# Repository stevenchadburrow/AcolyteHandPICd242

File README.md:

# AcolyteHandPICd242

This is the Acolyte Hand PIC'd 242, containing two PIC24 microcontrollers:  
The PIC24EP512GP202 and the PIC24FJ128GB202.  
The 'EP does all of the graphics, sound, and button inputs.  
The 'FJ is exclusively designed to be used as a USB host for HID and MSD.

The board is an all through-hole design for easy soldering.

Much of the code will be reused from the Acolyte Hand PIC'd 24 project.

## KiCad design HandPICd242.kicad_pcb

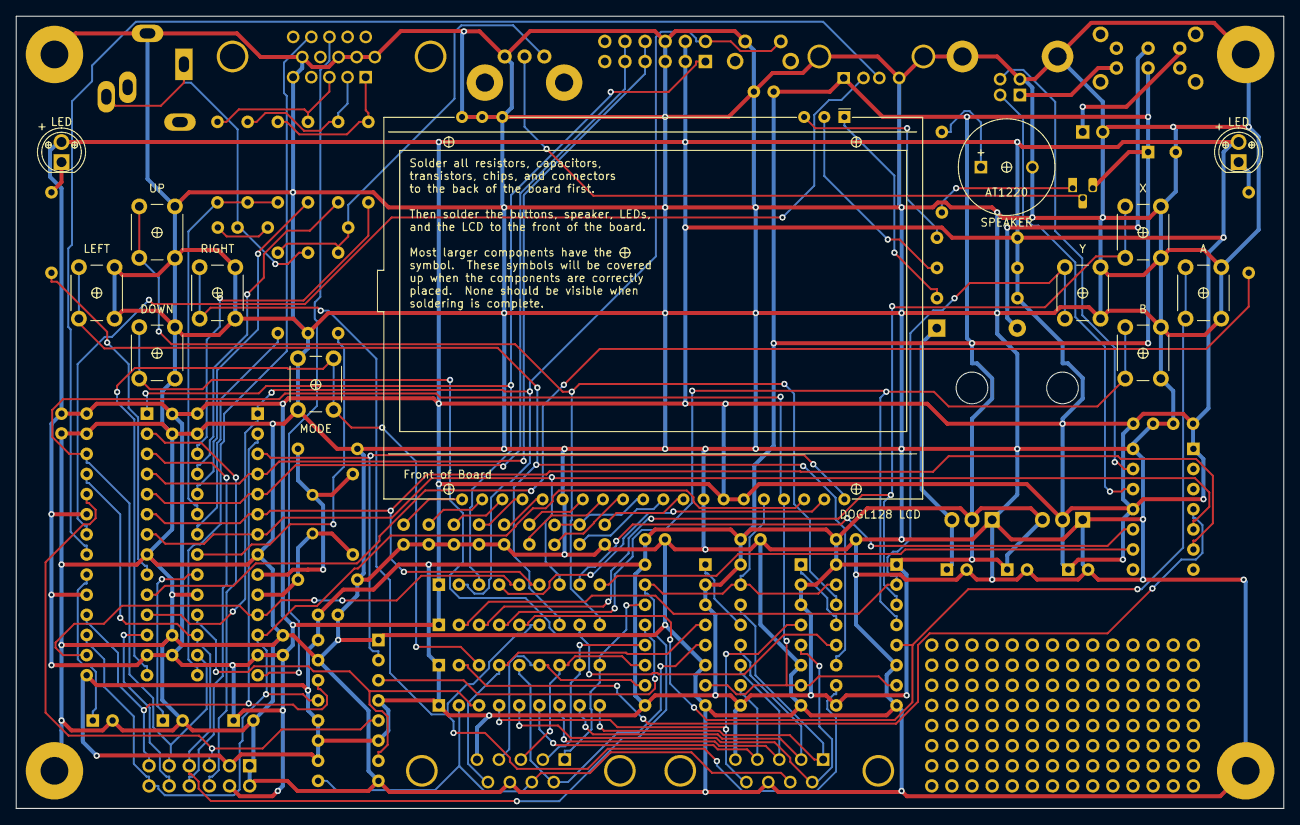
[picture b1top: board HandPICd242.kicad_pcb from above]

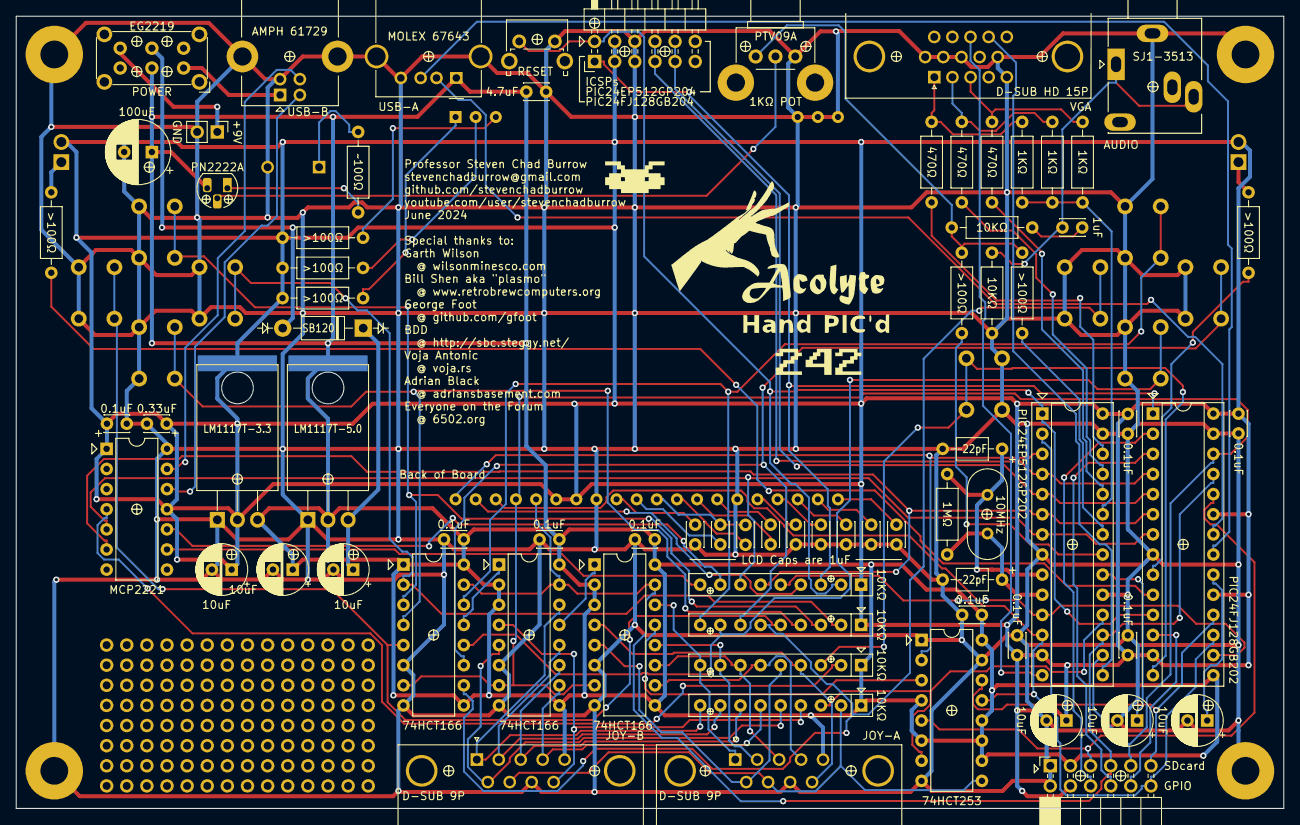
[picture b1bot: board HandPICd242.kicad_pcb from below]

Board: 2 copper layers, 160.0 x 100.0 mm, 101 parts (84 on the bottom side), 96 nets.

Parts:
C1, C2, C3, C6, C10, C13, C14, C16, C17, C18, C21, C22, C23, C24, C25, C26, C27, C28, C29, C30, C31: C_Small; C_Disc_D3.0mm_W2.0mm_P2.50mm
C4, C7, C8, C9, C12, C15: C_Polarized_Small_US; CP_Radial_D6.3mm_P2.50mm
C5: C_Polarized_US; CP_Radial_D8.0mm_P3.50mm
C19, C20: C; C_Axial_L3.8mm_D2.6mm_P7.50mm_Horizontal
D1, D2: LED; CustomLED
D3: D; D_DO-41_SOD81_P10.16mm_Horizontal
G101: LOGO; AcolyteTitle
G102: LOGO; HandPickedTitle
G103: LOGO; Mystery
G105: LOGO; ModelNum
G106: LOGO; HandPinching
J1: USB_B; USB_B_Lumberg_2411_02_Horizontal
J3: USB_A; USB_A_Molex_67643_Horizontal
J4, J19: DE9_Plug; DSUB-9_Male_Horizontal_P2.77x2.84mm_EdgePinOffset7.70mm_Hou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
J5: AudioJack3; BIGJack_3.5mm_Ledino_KB3SPRS_Horizontal
J6: DE15_Receptacle_HighDensity; DSUB-15-HD_Female_Horizontal_P2.29x2.54mm_VGA
J7: Conn_02x06_Odd_Even; PinSocket_2x06_P2.54mm_Horizontal
J9, J11, J12, J13: Conn_02x14_Odd_Even; BLANK-PinHeader_2x14_P2.54mm_Vertical
J14: Conn_02x06_Odd_Even; PinHeader_2x06_P2.54mm_Horizontal
J21: Conn_01x02; PinHeader_1x02_P2.54mm_Vertical
LS1: Speaker; MagneticBuzzer_ProSignal_ABT-410-RC
Q1: PN2222A; TO-92_HandSolder
R1, R2, R3, R4, R6, R7, R8, R9, R10, R11, R12, R13, R14, R15, R16, R18, R19: R_US; R_Axial_DIN0207_L6.3mm_D2.5mm_P10.16mm_Horizontal
RN1, RN2, RN3, RN4: R_Network08_US; R_Array_SIP9
RV1: R_Potentiometer_US; Potentiometer_Bourns_PTV09A-2_Single_Horizontal
SW1: SW_Push_DPDT; SW_E-Switch_EG2219_DPDT_Angled
SW3, SW4, SW5, SW6, SW7, SW8, SW9, SW10, SW13: SW_Push; SW_PUSH_6mm_H5mm
SW11: SW_Push; SW_Tactile_SPST_Angled_PTS645Vx83-2LFS
TP2, TP3, TP4, TP5: TestPoint; ScrewHole-4-40
U1: LM1117T-3.3; TO-220-3_Horizontal_TabDown-custom
U2: LM1117T-5.0; TO-220-3_Horizontal_TabDown-custom
U3: EA_DOGL128X-6; EA_DOGL128-6
U4: MCP2221AxSL; DIP-14_W7.62mm
U5: PIC24EP512GP202; DIP-28_W7.62mm_Socket
U6: PIC24FJ128GB202; DIP-28_W7.62mm_Socket
U7, U8, U9: 74HCT166; DIP-16_W7.62mm
U10: 74HCT253; DIP-16_W7.62mm
Y1: Crystal; Crystal_HC49-4H_Vertical

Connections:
+3V3: C1.1, C2.2, C3.2, C8.1, C12.1, C13.2, C14.2, C18.2, D1.2 (A), D2.2 (A), J7.4, J14.3, J14.4, R6.1, R18.1, R19.1, RN2.1 (common), RN4.1 (common), U1.2 (VO), U3.34 (VDD2), U3.35 (VDD), U4.1 (VDD), U4.11 (VUSB), U5.13 (VDD), U5.28 (AVDD), U6.13 (VDD), U6.19 (VBAT), U6.23 (Vusb3V3), U6.28 (VDD)
+5V: C5.1, C6.2, C15.1, C16.1, C17.1, C30.1, C31.1, J3.1 (VBUS), J4.5, J7.3, J19.5, Q1.3 (C), RN1.1 (common), RN3.1 (common), SW1.2 (B), U1.3 (VI), U2.2 (VO), U6.15 (RB6/RP6/Vbus*), U7.2 (A), U7.3 (B), U7.9 (Clr), U7.16 (VCC), U8.1 (Ds), U8.9 (Clr), U8.16 (VCC), U9.2 (A), U9.3 (B), U9.9 (Clr), U9.16 (VCC), U10.4 (I2a), U10.6 (I0a), U10.10 (I0b), U10.11 (I1b), U10.12 (I2b), U10.16 (VCC)
+9V: J21.1, SW1.6 (C)
AUDIO-COMBINED: R8.2, R9.1, R10.1, RV1.3
AUDIO-NEG: C10.2, R8.1
AUDIO-OUT: C10.1, J5.R, J5.T, R7.2
AUDIO-SOURCE-A: R10.2, U5.22 (RB11/RP43*+)
AUDIO-SOURCE-B: R9.2, U5.21 (RB10/RP42*+)
BLUE: J6.3, R13.2, R16.2
BUTTON-A: RN4.5 (R4), SW7.1, U8.5 (D)
BUTTON-B: RN4.4 (R3), SW8.1, U8.4 (C)
BUTTON-DOWN: RN4.8 (R7), SW4.1, U8.12 (G)
BUTTON-LEFT: RN4.7 (R6), SW5.1, U8.11 (F)
BUTTON-MODE: RN1.3 (R2), SW13.1, U6.14 (RB5/USBID*)
BUTTON-RIGHT: RN4.6 (R5), SW6.1, U8.10 (E)
BUTTON-UP: RN4.9 (R8), SW3.1, U8.14 (H)
BUTTON-X: RN4.3 (R2), SW9.1, U8.3 (B)
BUTTON-Y: RN4.2 (R1), SW10.1, U8.2 (A)
DS-A: U7.13 (Qh), U9.1 (Ds)
DS-B: U7.1 (Ds), U8.13 (Qh)
GND: C1.2, C2.1, C3.1, C4.2, C5.2, C6.1, C7.2, C8.2, C9.2, C12.2, C13.1, C14.1, C15.2, C16.2, C17.2, C18.1, C19.2, C20.2, C24.2, C25.2, C26.2, C27.2, C28.2, C29.2, C30.2, C31.2, J1.4 (GND), J1.5 (Shield), J3.4 (GND), J3.5 (Shield), J4.8, J5.S, J6.5, J6.6, J6.7, J6.8, J6.10, J7.1, J7.2, J14.5, J14.6, J19.8, J21.2, LS1.2, R7.1, RV1.1, SW3.2, SW4.2, SW5.2, SW6.2, SW7.2, SW8.2, SW9.2, SW10.2, SW11.2, SW13.2, TP2.1, TP3.1, TP4.1, TP5.1, U1.1 (GND), U2.1 (GND), U3.18 (C1-), U3.19 (C2-), U3.20 (C3-), U3.26 (VSS), U3.33 (VSS), U4.14 (VSS), U5.8 (VSS), U5.19 (VSS), U5.27 (AVSS), U6.8 (VSS), U6.27 (VSS), U7.6 (CE), U7.8 (GND), U8.6 (CE), U8.8 (GND), U9.6 (CE), U9.8 (GND), U10.1 (OEa), U10.8 (GND), U10.15 (OEb)
GPIO-RA0: J7.6, U6.2 (RA0/RP5/PGED3/ASDA1)
GPIO-RA1: J7.8, U6.3 (RA1/RP6/PGEC3/ASCL1)
GPIO-RA4: J7.10, U6.12 (RA4*)
GREEN: J6.2, R12.2, R15.2
H-SYNC: J6.13, U5.14 (RB5/RP37/ASDA2/PGED2*)
ICSP-CLK: J14.9, J14.10, U5.5 (RB1/RPI33/PGEC3), U6.5 (RB1/RP1/PGEC1)
ICSP-DAT: J14.7, J14.8, U5.4 (RB0/RPI32/PGED3), U6.4 (RB0/RP0/PGED1)
INTERRUPT: RN2.5 (R4), U5.11 (RB4/RP36*), U6.16 (RB7/RP7/INT0*)
JOY-BUTTON1-A: J4.6, RN1.5 (R4), U9.5 (D)
JOY-BUTTON1-B: J19.6, RN3.5 (R4), U7.5 (D)
JOY-BUTTON2-A: J4.9, RN1.4 (R3), U9.4 (C)
JOY-BUTTON2-B: J19.9, RN3.4 (R3), U7.4 (C)
JOY-DOWN-A: J4.2, RN1.8 (R7), U9.12 (G)
JOY-DOWN-B: J19.2, RN3.8 (R7), U7.12 (G)
JOY-LEFT-A: J4.3, RN1.7 (R6), U9.11 (F)
JOY-LEFT-B: J19.3, RN3.7 (R6), U7.11 (F)
JOY-RIGHT-A: J4.4, RN1.6 (R5), U9.10 (E)
JOY-RIGHT-B: J19.4, RN3.6 (R5), U7.10 (E)
JOY-SELECT: J4.7, J19.7, RN3.2 (R1), U10.9 (Zb)
JOY-UP-A: J4.1, RN1.9 (R8), U9.14 (H)
JOY-UP-B: J19.1, RN3.9 (R8), U7.14 (H)
LED-A: R3.2, U6.9 (RA2/CLKI)
LED-B: R2.2, U6.10 (RA3/CLKO)
LED-MID-A: D1.1 (K), R3.1
LED-MID-B: D2.1 (K), R2.1
MCLKI: C19.1, R1.1, U5.9 (RA2/CLKI), Y1.1
MCLKO: C20.1, R1.2, U5.10 (RA3/CLKO+), Y1.2
unnamed: LS1.1, R4.2
unnamed: Q1.2 (B), RV1.2
unnamed: Q1.1 (E), R4.1
unnamed: R6.2, U3.1 (A1+)
unnamed: R18.2, U3.2 (A2+)
unnamed: R19.2, U3.3 (A3+)
unnamed: C21.1, C22.1, U3.30 (CAP1N)
unnamed: C22.2, U3.29 (CAP1P)
unnamed: C23.1, U3.27 (CAP2N)
unnamed: C23.2, U3.28 (CAP2P)
unnamed: C21.2, U3.31 (CAP3P)
unnamed: C24.1, U3.21 (V0)
unnamed: C25.1, U3.22 (V1)
unnamed: C26.1, U3.23 (V2)
unnamed: C27.1, U3.24 (V3)
unnamed: C28.1, U3.25 (V4)
unnamed: C29.1, U3.32 (VOUT)
PIX-BLUE: R13.1, U5.24 (RB13/RPI45*+)
PIX-GREEN: R12.1, U5.25 (RB14/RPI46*+)
PIX-INTENSITY: R14.1, R15.1, R16.1, U5.23 (RB12/RBI44*+)
PIX-RED: R11.1, U5.26 (RB15/RPI47*+)
PWR-BAT: D3.2 (A), SW1.5 (B)
PWR-USB: J1.1 (VBUS), SW1.1 (A)
RED: J6.1, R11.2, R14.2
RX-A/TX-B: RN2.6 (R5), U4.6 (UTx), U5.6 (RB2/RPI34/PGEC1), U6.6 (RB2/RP2/SDA2)
SCL: RN2.8 (R7), U4.10 (SCL)
SDA: RN2.9 (R8), U4.9 (SDA)
SPI-CLK: J7.9, U3.37 (SCL), U5.16 (RB7/RP39/SCK1/INT0+), U6.26 (RB15/RP15), U7.7 (Clk), U8.7 (Clk), U9.7 (Clk)
SPI-CS-A: J7.11, U5.2 (RA0), U6.18 (RB9/RP9/SDA1), U10.14 (A0)
SPI-CS-B: U3.40 (~CS1B), U5.3 (RA1), U10.2 (A1)
SPI-MISO: RN3.3 (R2), U5.18 (RB9/RP41/SDI1/ASDA1*+), U10.7 (Za)
SPI-MISO-A: J7.5, U6.24 (RB13/RP13), U10.5 (I1a)
SPI-MISO-B: U9.13 (Qh), U10.3 (I3a)
SPI-MOSI: J7.7, U3.36 (SI), U5.17 (RB8/RP40/SDO1/ASCL1+), U6.25 (RB14/RP14), U7.15 (PE), U8.15 (PE), U9.15 (PE)
SPI-SELECT: J7.12, U3.38 (A0), U5.12 (RA4/RP20+), U6.17 (RB8/RP8/SCL1/USBOEN*), U10.13 (I3b)
TX-A/RX-B: RN2.7 (R6), U4.5 (URx), U5.7 (RB3/RP35/PGED1), U6.7 (RB3/RP3/SCL2)
USB-A-D+: J3.3 (D+), U6.21 (RB10/RP10/PGED2/D+*)
USB-A-D-: J3.2 (D-), U6.22 (RB11/RP11/PGEC2/D-*)
USB-B-D+: J1.3 (D+), U4.13 (D+)
USB-B-D-: J1.2 (D-), U4.12 (D-)
V-REG: C4.1, D3.1 (K), U2.3 (VI)
V-SYNC: J6.14, U5.15 (RB6/RP38/ASCL2/PGEC2*)
VCAP-A: C7.1, U5.20 (VCAP)
VCAP-B: C9.1, U6.20 (VCAP)
~MCLR-A: J14.2, RN2.2 (R1), SW11.1, U5.1 (~MCLR*), U6.11 (RB4/RPI4*)
~MCLR-B: J14.1, RN2.3 (R2), U6.1 (~MCLR)
~MCLR-C: RN2.4 (R3), U3.39 (~RST)
~MCLR-D: RN1.2 (R1), U4.4 (~RST)
